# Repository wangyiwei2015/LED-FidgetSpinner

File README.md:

# LED-FidgetSpinner
Battery-powered LED Fidget Spinner. **PhOVS**

Design & concept reference: [8Mode Fidget Spinner](https://www.8mode.com/spinner/)

Warning: this is still under development.

Warning: there maybe better MCU model for this application.

### Development Tools

PCB: **KiCAD**

​    --> ./FidgetSpinner-PCB/

Firmware: **STM32CubeMX** & **CLion**

​    --> ./FidgetSpinner-FW/STM32L010_CLion/

3D Models: **Shapr3D** for iPad

​    --> ./FidgetSpinner-Struct/

### BOM

| Name           | Model         | Package | Quantity | Price (CNY each) |
| -------------- | ------------- | ------- | -------- | ---------------- |
| MCU            | STM32L010K8T6 |         | 1        | 33               |
| Regulator      | BL8530        |         | 1        | 0.16             |
| Optical Sensor | GP2S60        |         | 1        | 3.50             |
| Switch         | MSK-12C02     |         | 1        | 0.16             |
| Button         |               |         | 1        |                  |
| Battery        | CR2450        | CR2450  | 3        |                  |
| Battery Case   |               |         | 3        |                  |
| LED            | warm-white    | 0805    | 8        |                  |
| Diode          | D             | 0805    | 2        | 0.06             |
| L              | 47uH          | 0805    | 1        |                  |
| C              | 100nF         | 0805    | 3        |                  |
| C              | 1uF           | 0805    | 1        |                  |
| C              | 47uF          | 0805    | 1        |                  |
| R_LED          | 1k1           | 0805    | 8        |                  |
| R_IR           | 3k3           | 0805    | 1        |                  |
| R_Comp         | 20k           | 0805    | 1        |                  |
| R_Comp         | 33k           | 0805    | 1        |                  |
| R_Tr           | 1M            | 0805    | 1        |                  |
| R              | 10k           | 0805    | 3        |                  |

Different coin-sized 3V battery cells

| Name   | Capacity(mAh) | I(uA) | Ic(mA) | Imax(mA) | Weight(g) |
| ------ | ------------- | ----- | ------ | -------- | --------- |
| CR2477 | 950           | 200   | 3      | 20       | 9.9       |
| CR2450 | 550           | 200   | 3      | 20       | 5.8       |
| CR2430 | 270           | 200   | 3      | 20       | 4.3       |
| CR3032 | 550           | 200   | 3      | 20       | 6.8       |
| CR2032 | 210           | 200   | 2      | 20       | 3.0       |
| CR2025 | 150           | 200   | 2      | 20       | 2.5       |

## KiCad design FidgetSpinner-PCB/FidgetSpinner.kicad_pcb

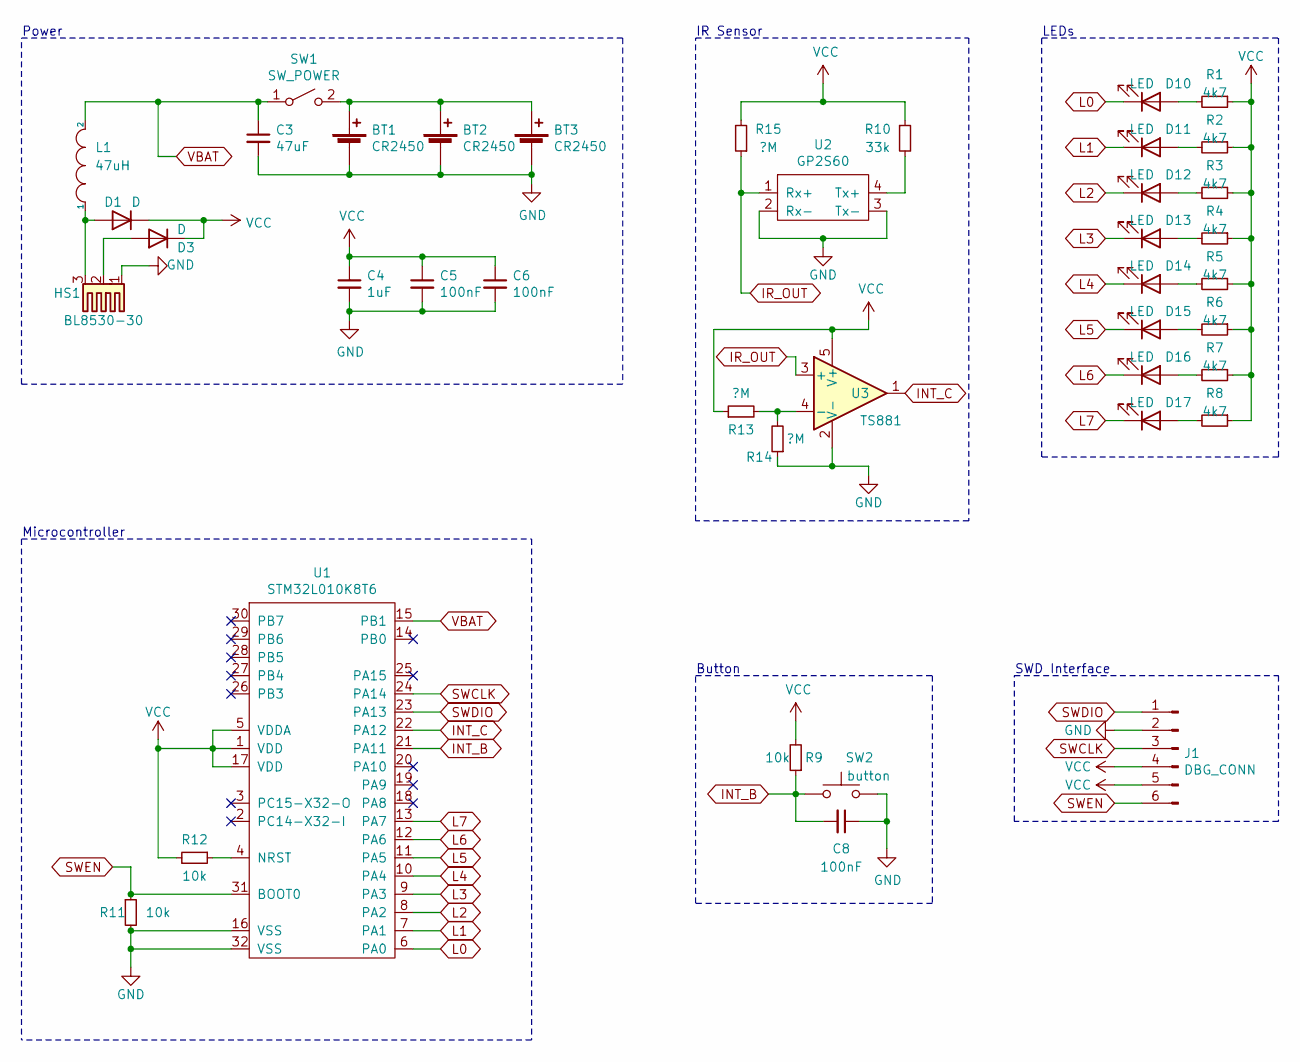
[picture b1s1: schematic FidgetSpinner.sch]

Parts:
BT1, BT2, BT3: CR2450; BatteryHolder_Keystone_3009_1x2450
C3: 47uF; C_0805_2012Metric_Pad1.18x1.45mm_HandSolder
C4: 1uF; C_0805_2012Metric_Pad1.18x1.45mm_HandSolder
C5, C6, C8: 100nF; C_0805_2012Metric_Pad1.18x1.45mm_HandSolder
D1, D3: D; D_0805_2012Metric_Pad1.15x1.40mm_HandSolder
D10, D11, D12, D13, D14, D15, D16, D17: LED; D_0805_2012Metric_Pad1.15x1.40mm_HandSolder
HS1: BL8530-30; SOT-89-3_Handsoldering
J1: DBG_CONN; PinHeader_1x06_P2.54mm_Horizontal
L1: 47uH; L_0805_2012Metric_Pad1.15x1.40mm_HandSolder
R1, R2, R3, R4, R5, R6, R7, R8: 4k7; R_0805_2012Metric_Pad1.20x1.40mm_HandSolder
R9, R11, R12: 10k; R_0805_2012Metric_Pad1.20x1.40mm_HandSolder
R10: 33k; R_0805_2012Metric_Pad1.20x1.40mm_HandSolder
R13, R14, R15: ?M; R_0805_2012Metric_Pad1.20x1.40mm_HandSolder
SW1: SW_POWER; SW_SPDT_PCM12
SW2: button; SW_SPST_SKQG_WithStem
U1: STM32L010K8T6; LQFP-32_7x7mm_P0.8mm
U2: GP2S60; GP2S60_3217
U3: TS881; SOT-353_SC-70-5

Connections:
GND: BT1.2 (-), BT2.2 (-), BT3.2 (-), C3.2, C4.2, C5.2, C6.2, C8.1, HS1.1, J1.2, R11.2, R14.1, SW2.2, U1.16 (VSS), U1.32 (VSS), U2.2 (Rx-), U2.3 (Tx-), U3.2 (V-); also elsewhere on the board
INT_B: C8.2, R9.1, SW2.1, U1.21 (PA11)
INT_C: U1.22 (PA12), U3.1; also elsewhere on the board
IR_OUT: R15.1, U2.1 (Rx+), U3.3 (+); also elsewhere on the board
L0: D10.1 (K), U1.6 (PA0)
L1: D11.1 (K), U1.7 (PA1)
L2: D12.1 (K), U1.8 (PA2)
L3: D13.1 (K), U1.9 (PA3)
L4: D14.1 (K), U1.10 (PA4)
L5: D15.1 (K), U1.11 (PA5)
L6: D16.1 (K), U1.12 (PA6)
L7: D17.1 (K), U1.13 (PA7)
unnamed: BT1.1 (+), BT2.1 (+), BT3.1 (+), SW1.2 (B)
unnamed: D1.2 (A), HS1.3, L1.1
unnamed: D3.2 (A), HS1.2
unnamed: D10.2 (A), R1.2
unnamed: D11.2 (A), R2.2
unnamed: D12.2 (A), R3.2
unnamed: D13.2 (A), R4.2
unnamed: D14.2 (A), R5.2
unnamed: D15.2 (A), R6.2
unnamed: D16.2 (A), R7.2
unnamed: D17.2 (A), R8.2
unnamed: R10.2, U2.4 (Tx+)
unnamed: R12.1, U1.4 (NRST)
unnamed 25: R13.2, R14.2, U3.4 (-); also elsewhere on the board
SWCLK: J1.3, U1.24 (PA14)
SWDIO: J1.1, U1.23 (PA13)
SWEN: J1.6, R11.1, U1.31 (BOOT0)
VBAT: C3.1, L1.2, SW1.1 (A), U1.15 (PB1)
VCC: C4.1, C5.1, C6.1, D1.1 (K), D3.1 (K), J1.4, J1.5, R1.1, R2.1, R3.1, R4.1, R5.1, R6.1, R7.1, R8.1, R9.2, R10.1, R12.2, R13.1, R15.2, U1.1 (VDD), U1.5 (VDDA), U1.17 (VDD), U3.5 (V+); also elsewhere on the board

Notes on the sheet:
Power
SWD Interface
Button
IR Sensor
LEDs
Microcontroller

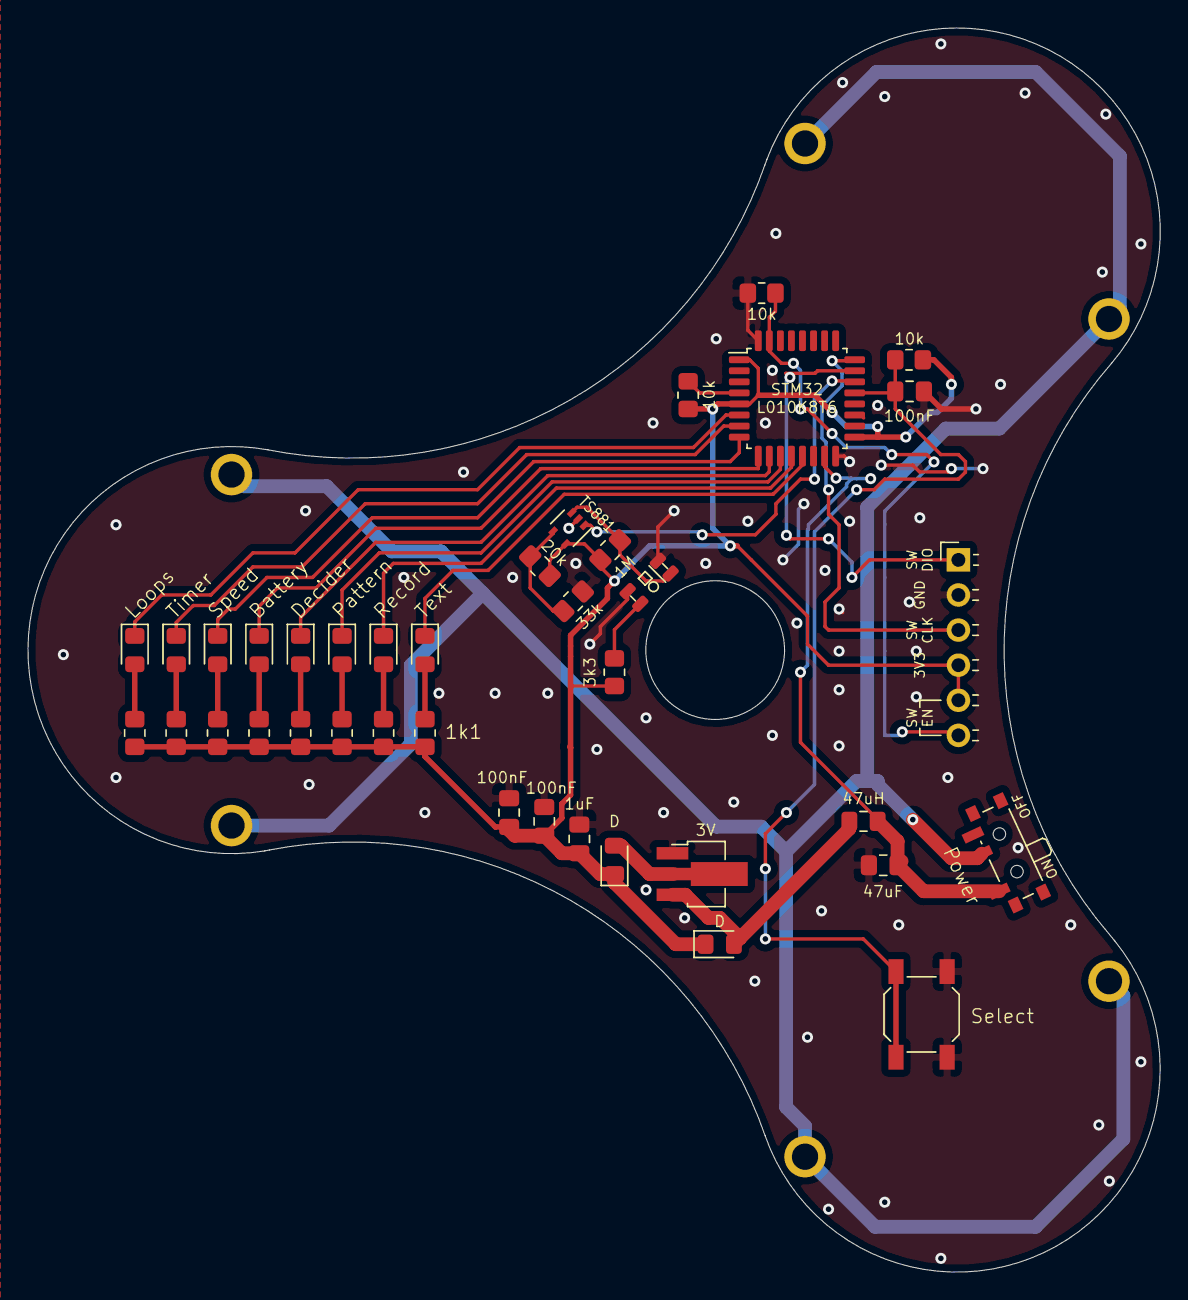
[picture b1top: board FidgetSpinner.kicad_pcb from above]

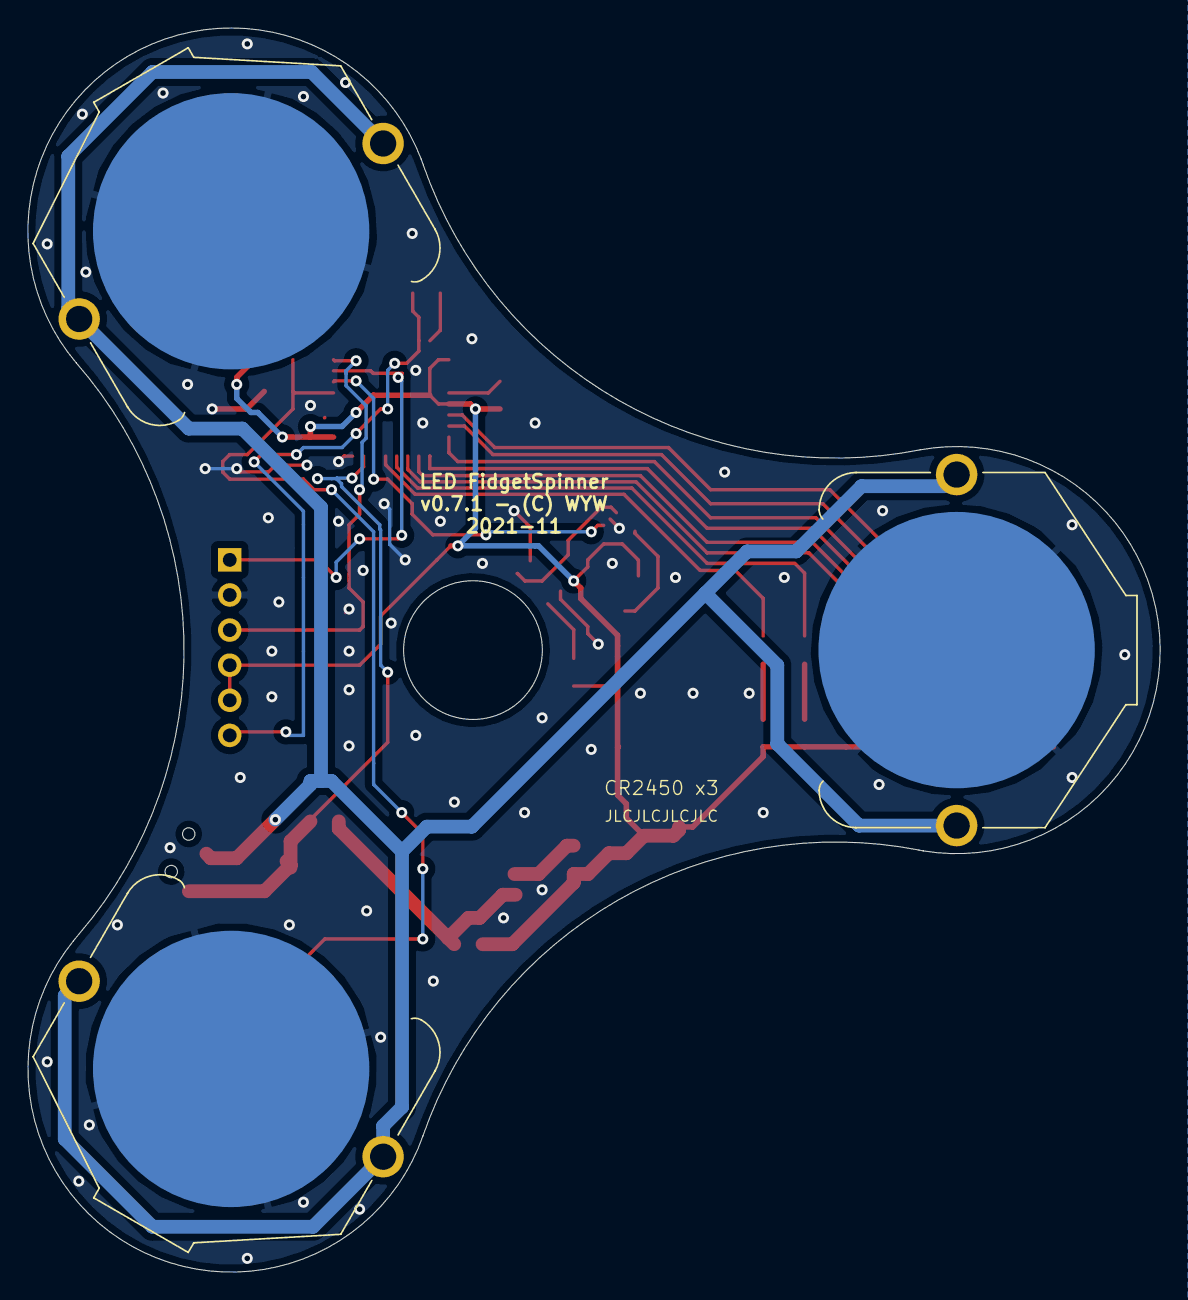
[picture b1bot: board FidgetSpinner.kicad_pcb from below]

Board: 2 copper layers, 81.9 x 90.0 mm, 41 parts (3 on the bottom side), 31 nets.

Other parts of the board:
TS881: TS881; SOT-353_SC-70-5

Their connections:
GND: TS881.2; also elsewhere on the board
INT_C: TS881.1; also elsewhere on the board
IR_OUT: TS881.3; also elsewhere on the board
unnamed 25: TS881.4; also elsewhere on the board
VCC: TS881.5; also elsewhere on the board

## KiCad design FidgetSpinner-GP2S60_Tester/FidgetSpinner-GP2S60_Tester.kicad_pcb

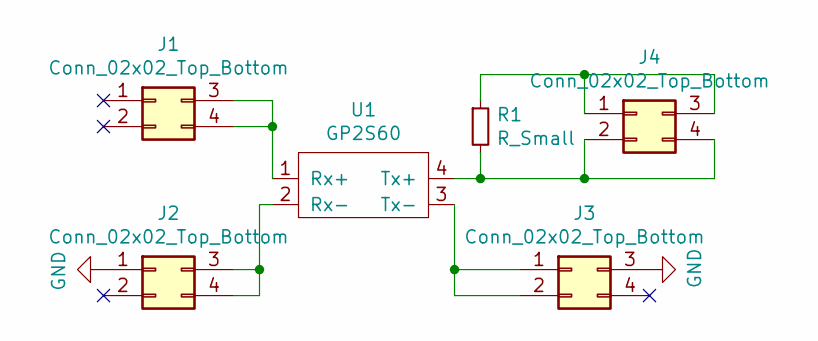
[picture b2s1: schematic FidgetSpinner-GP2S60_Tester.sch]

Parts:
J1, J2, J3, J4: Conn_02x02_Top_Bottom; PinHeader_2x02_P2.54mm_Vertical
R1: R_Small; R_0805_2012Metric_Pad1.20x1.40mm_HandSolder
U1: GP2S60; GP2S60_3217

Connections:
GND: J2.1, J3.3
unnamed: J1.3, J1.4, U1.1 (Rx+)
unnamed: J2.3, J2.4, U1.2 (Rx-)
unnamed: J3.1, J3.2, U1.3 (Tx-)
unnamed: J4.1, J4.3, R1.1
unnamed: J4.2, J4.4, R1.2, U1.4 (Tx+)

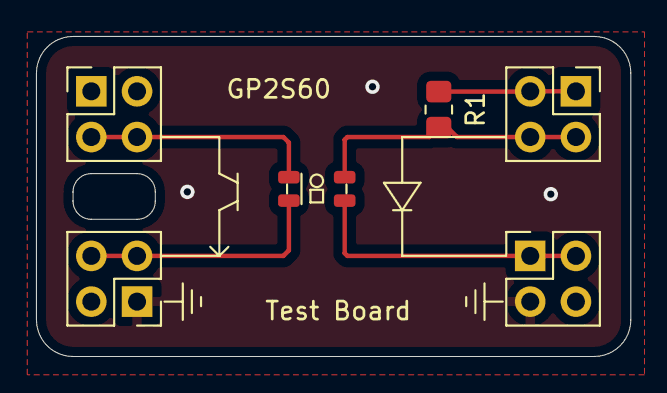
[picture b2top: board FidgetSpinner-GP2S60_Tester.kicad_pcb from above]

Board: 2 copper layers, 33.0 x 17.8 mm, 6 parts (0 on the bottom side), 6 nets.

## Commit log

2021-08-30 init pcb v0.1.0
2021-08-30 fixed: CR2477 label
2021-09-03 init firmware ATSAM
2021-09-03 changed to STM32L0 MCU
2021-09-04 changed to STM32 and CR2450
2021-09-04 added eSWD dbg board
2021-09-06 button animations
2021-09-12 fixed holes and gnd
2021-09-16 backup of CLion project
2021-09-17 updated edge conn
2021-09-17 added ADC feature
2021-09-17 added battery to ADC connection for PCB
2021-09-17 regenerated codes and project files
    due to a strange error
2021-09-19 added features
2021-09-19 backup
2021-09-19 optimized codes and added ADC config MX
2021-09-19 added EEPROM IO
2021-09-19 added best score
2021-09-20 using GP2S27 optic sensor
2021-09-20 updated PCB
2021-09-22 tested and fixed: ADC and EEPROM
2021-09-27 important updates
2021-09-27 removed edge connector
2021-09-27 optimized labels
2021-10-10 added GP2S60 test board
2021-10-15 bug fixes
2021-11-04 resistor value & firmware updates
2021-11-06 rearranged files
2022-01-01 unknown update
2022-12-17 updated caps
